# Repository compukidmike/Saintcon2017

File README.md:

# Saintcon 2017
These are the files for the stuff I worked on for Saintcon 2017

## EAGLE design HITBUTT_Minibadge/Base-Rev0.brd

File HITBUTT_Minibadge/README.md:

# HITBUTT Minibadge

I worked on the Hak In The Box (@HITBUTT) minibadge for Saintcon 2017. I'll update this with more info during/after the con.

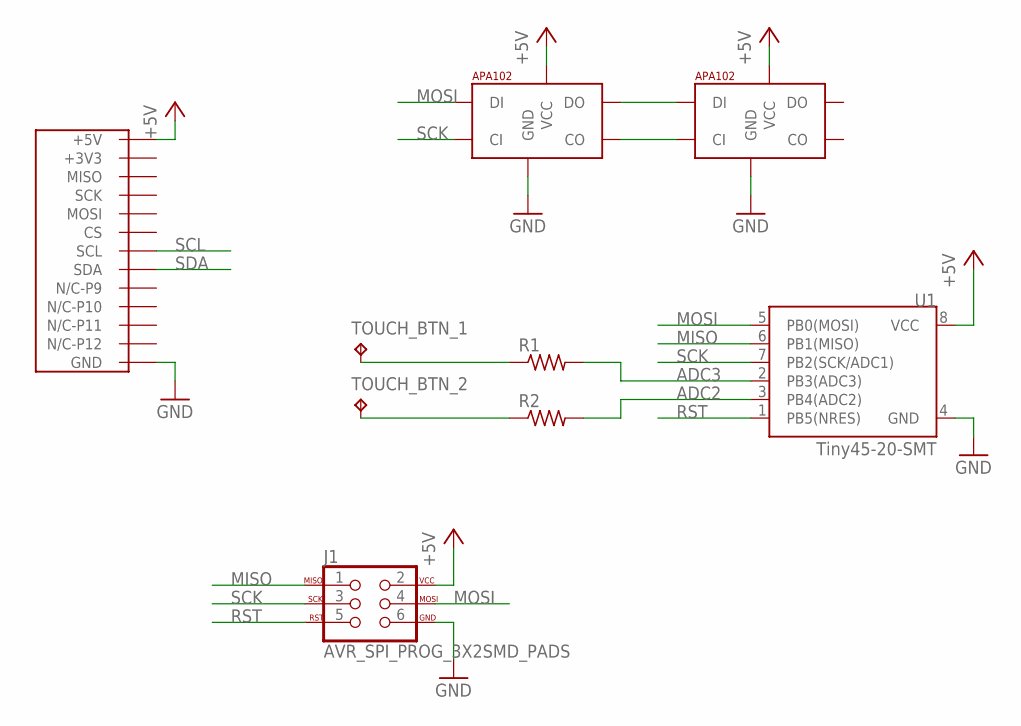
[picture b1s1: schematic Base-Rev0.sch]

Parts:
J1: AVR_SPI_PROG_3X2SMD_PADS; 2X3-SMD-PADS
R1, R2: R-US_M0805; M0805
TOUCH_BTN_1, TOUCH_BTN_2: TPTP06R; TP06R
U1: Tiny45-20-SMT; SO08-EIAJ_MCU
U2, U3: APA1025050; APA102_5050
U$1: BADGE64EXAMPLE; BADGE64-MINIBADGE

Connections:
+3V3: U$1.+3V3-P7 (+3V3), U$1.+3V3-P15 (+3V3)
+5V: J1.2, U1.8 (VCC), U2.1 (VCC), U3.1 (VCC), U$1.+5V
ADC2: R2.2, U1.3 (PB4(ADC2))
ADC3: R1.2, U1.2 (PB3(ADC3))
BTN2: R2.1, TOUCH_BTN_2.TP
GND: J1.6, U1.4 (GND), U2.6 (GND), U3.6 (GND), U$1.GND-P2 (GND), U$1.GND-P8 (GND), U$1.GND-P16 (GND)
MISO: J1.1, U1.6 (PB1(MISO))
MOSI: J1.4, U1.5 (PB0(MOSI)), U2.4 (DI)
unnamed: U2.2 (CO), U3.5 (CI)
unnamed: U2.3 (DO), U3.4 (DI)
unnamed: R1.1, TOUCH_BTN_1.TP
RST: J1.5, U1.1 (PB5(NRES))
SCK: J1.3, U1.7 (PB2(SCK/ADC1)), U2.5 (CI)
SCL: U$1.SCL
SDA: U$1.SDA

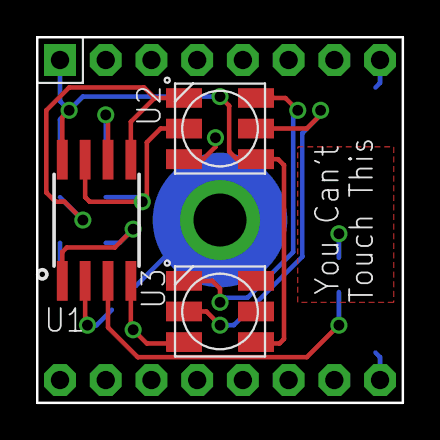
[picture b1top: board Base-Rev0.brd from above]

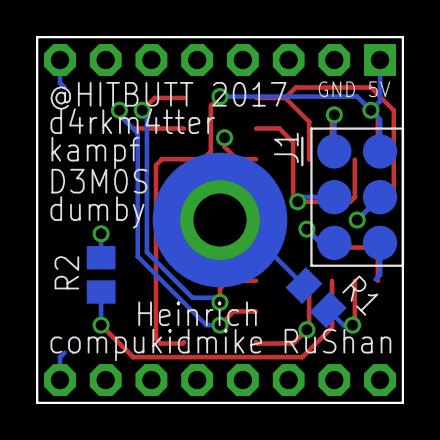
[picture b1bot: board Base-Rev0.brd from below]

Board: 2 copper layers, 20.3 x 20.3 mm, 9 parts (5 on the bottom side), 13 nets.

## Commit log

2017-10-05 initial readme commit

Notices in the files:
parts and their libraries:
SparkFun-Connectors: Licensing: Creative Commons ShareAlike 4.0 International - https://creativecommons.org/licenses/by-sa/4.0
